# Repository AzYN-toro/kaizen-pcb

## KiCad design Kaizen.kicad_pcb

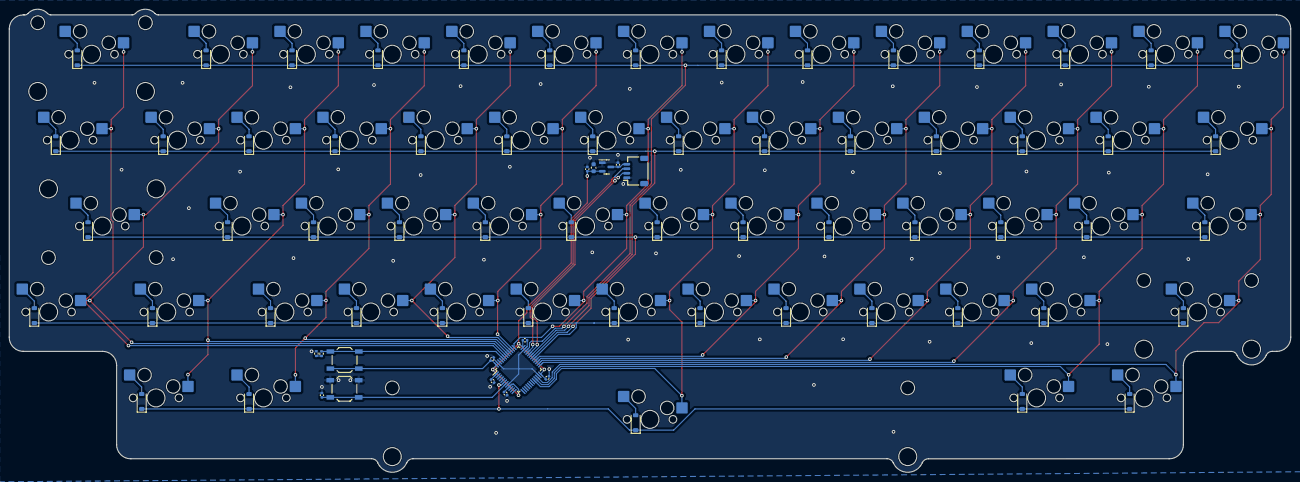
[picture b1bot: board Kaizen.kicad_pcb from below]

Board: 2 copper layers, 284.2 x 102.7 mm, 134 parts (134 on the bottom side), 86 nets.

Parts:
BOOT1: SW_SPST; SW_SPST_TL3342
C1: 10uF; C_0603_1608Metric
C2, C3, C4, C5, C6, C8: 100nF; C_0402_1005Metric
C9, C10: 1uF; C_0402_1005Metric
D1, D2, D3, D4, D5, D6, D7, D8, D9, D10, D11, D12, D13, D14, D15, D16, D17, D18, D19, D20, D21, D22, D23, D24, D25, D26, D27, D28, D29, D30, D31, D32, D33, D34, D35, D36, D37, D38, D39, D40, D41, D42, D43, D44, D45, D46, D47, D48, D49, D50, D51, D52, D53, D54, D55, D56, D57, D58, D59: D_Small; D_SOD-123
J1: PCB Connector; JST_SH_SM04B-SRSS-TB_1x04-1MP_P1.00mm_Horizontal
R2, R4: 5.1k; R_0402_1005Metric
RST1: SW_SPST; SW_SPST_TL3342
SW1, SW2, SW3, SW4, SW5, SW6, SW7, SW8, SW9, SW10, SW11, SW12, SW13, SW16, SW17, SW18, SW19, SW20, SW21, SW22, SW23, SW24, SW25, SW26, SW27, SW29, SW30, SW31, SW32, SW33, SW34, SW35, SW36, SW37, SW38, SW39, SW40, SW43, SW44, SW45, SW46, SW47, SW48, SW49, SW50, SW51, SW52, SW54, SW55, SW58: SW_Push_45deg; MX-Hotswap-1U
SW14: SW_Push_45deg; MX-Hotswap-2U
SW15, SW28, SW56, SW57: SW_Push_45deg; MX-Hotswap-1.5U
SW41: SW_Push_45deg; MX-Hotswap-2.25U-ReversedStabilizers
SW42: SW_Push_45deg; MX-Hotswap-2.25U
SW53: SW_Push_45deg; MX-Hotswap-1.75U
SW59: SW_Push_45deg; MX-Hotswap-7U
U1: STM32F072CBT6; LQFP-48_7x7mm_P0.5mm
U3: XC6206PxxxMR-Regulator_Linear; SOT-23

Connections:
+3V3: BOOT1.1 (A), C1.1, C2.1, C3.1, C4.1, C5.1, C6.1, C10.1, U1.1 (VBAT), U1.9 (VDDA), U1.24 (VDD), U1.36 (VDDIO2), U1.48 (VDD), U3.2 (VO)
+5V: C9.1, J1.4, U3.3 (VI)
BOOT0: BOOT1.2 (B), R2.1, U1.44 (BOOT0)
Col0: SW1.1, SW15.1, SW29.1, SW42.1, SW55.1, U1.22 (PB11)
Col1: SW2.1, SW16.1, SW30.1, SW43.1, SW56.1, U1.21 (PB10)
Col2: SW3.1, SW17.1, SW31.1, SW44.1, U1.25 (PB12)
Col3: SW4.1, SW18.1, SW32.1, SW45.1, U1.26 (PB13)
Col4: SW5.1, SW19.1, SW33.1, SW46.1, U1.27 (PB14)
Col5: SW6.1, SW20.1, SW34.1, SW47.1, U1.28 (PB15)
Col6: SW7.1, SW21.1, SW35.1, SW48.1, SW59.1, U1.20 (PB2)
Col7: SW8.1, SW22.1, SW36.1, SW49.1, U1.37 (PA14)
Col8: SW9.1, SW23.1, SW37.1, SW50.1, U1.38 (PA15)
Col9: SW10.1, SW24.1, SW38.1, SW51.1, U1.39 (PB3)
Col10: SW11.1, SW25.1, SW39.1, SW52.1, SW57.1, U1.40 (PB4)
Col11: SW12.1, SW26.1, SW40.1, SW53.1, SW58.1, U1.41 (PB5)
Col12: SW13.1, SW27.1, SW41.1, SW54.1, U1.42 (PB6)
Col13: SW14.1, SW28.1, U1.43 (PB7)
D+: J1.2, U1.33 (PA12)
D-: J1.3, U1.32 (PA11)
GND: C1.2, C2.2, C3.2, C4.2, C5.2, C6.2, C8.2, C9.2, C10.2, J1.1, R4.2, RST1.2 (B), U1.8 (VSSA), U1.23 (VSS), U1.35 (VSS), U1.47 (VSS), U3.1 (GND)
NRST: C8.1, RST1.1 (A), U1.7 (NRST)
unnamed: D1.2 (A), SW1.2
unnamed: D2.2 (A), SW2.2
unnamed: D3.2 (A), SW3.2
unnamed: D4.2 (A), SW4.2
unnamed: D5.2 (A), SW5.2
unnamed: D6.2 (A), SW6.2
unnamed: D7.2 (A), SW7.2
unnamed: D8.2 (A), SW8.2
unnamed: D9.2 (A), SW9.2
unnamed: D10.2 (A), SW10.2
unnamed: D11.2 (A), SW11.2
unnamed: D12.2 (A), SW12.2
unnamed: D13.2 (A), SW13.2
unnamed: D14.2 (A), SW14.2
unnamed: D15.2 (A), SW15.2
unnamed: D16.2 (A), SW16.2
unnamed: D17.2 (A), SW17.2
unnamed: D18.2 (A), SW18.2
unnamed: D19.2 (A), SW19.2
unnamed: D20.2 (A), SW20.2
unnamed: D21.2 (A), SW21.2
unnamed: D22.2 (A), SW22.2
unnamed: D23.2 (A), SW23.2
unnamed: D24.2 (A), SW24.2
unnamed: D25.2 (A), SW25.2
unnamed: D26.2 (A), SW26.2
unnamed: D27.2 (A), SW27.2
unnamed: D28.2 (A), SW28.2
unnamed: D29.2 (A), SW29.2
unnamed: D30.2 (A), SW30.2
unnamed: D31.2 (A), SW31.2
unnamed: D32.2 (A), SW32.2
unnamed: D33.2 (A), SW33.2
unnamed: D34.2 (A), SW34.2
unnamed: D35.2 (A), SW35.2
unnamed: D36.2 (A), SW36.2
unnamed: D37.2 (A), SW37.2
unnamed: D38.2 (A), SW38.2
unnamed: D39.2 (A), SW39.2
unnamed: D40.2 (A), SW40.2
unnamed: D41.2 (A), SW41.2
unnamed: D42.2 (A), SW42.2
unnamed: D43.2 (A), SW43.2
unnamed: D44.2 (A), SW44.2
unnamed: D45.2 (A), SW45.2
unnamed: D46.2 (A), SW46.2
unnamed: D47.2 (A), SW47.2
unnamed: D48.2 (A), SW48.2
unnamed: D49.2 (A), SW49.2
unnamed: D50.2 (A), SW50.2
unnamed: D51.2 (A), SW51.2
unnamed: D52.2 (A), SW52.2
unnamed: D53.2 (A), SW53.2
unnamed: D54.2 (A), SW54.2
unnamed: D55.2 (A), SW55.2
unnamed: D56.2 (A), SW56.2
unnamed: D57.2 (A), SW57.2
unnamed: D58.2 (A), SW58.2
unnamed: D59.2 (A), SW59.2
unnamed: R2.2, R4.1
Row0: D1.1 (K), D2.1 (K), D3.1 (K), D4.1 (K), D5.1 (K), D6.1 (K), D7.1 (K), D8.1 (K), D9.1 (K), D10.1 (K), D11.1 (K), D12.1 (K), D13.1 (K), D14.1 (K), U1.34 (PA13)
Row1: D15.1 (K), D16.1 (K), D17.1 (K), D18.1 (K), D19.1 (K), D20.1 (K), D21.1 (K), D22.1 (K), D23.1 (K), D24.1 (K), D25.1 (K), D26.1 (K), D27.1 (K), D28.1 (K), U1.31 (PA10)
Row2: D29.1 (K), D30.1 (K), D31.1 (K), D32.1 (K), D33.1 (K), D34.1 (K), D35.1 (K), D36.1 (K), D37.1 (K), D38.1 (K), D39.1 (K), D40.1 (K), D41.1 (K), U1.30 (PA9)
Row3: D42.1 (K), D43.1 (K), D44.1 (K), D45.1 (K), D46.1 (K), D47.1 (K), D48.1 (K), D49.1 (K), D50.1 (K), D51.1 (K), D52.1 (K), D53.1 (K), D54.1 (K), U1.29 (PA8)
Row4: D55.1 (K), D56.1 (K), D57.1 (K), D58.1 (K), D59.1 (K), U1.6 (PF1)
